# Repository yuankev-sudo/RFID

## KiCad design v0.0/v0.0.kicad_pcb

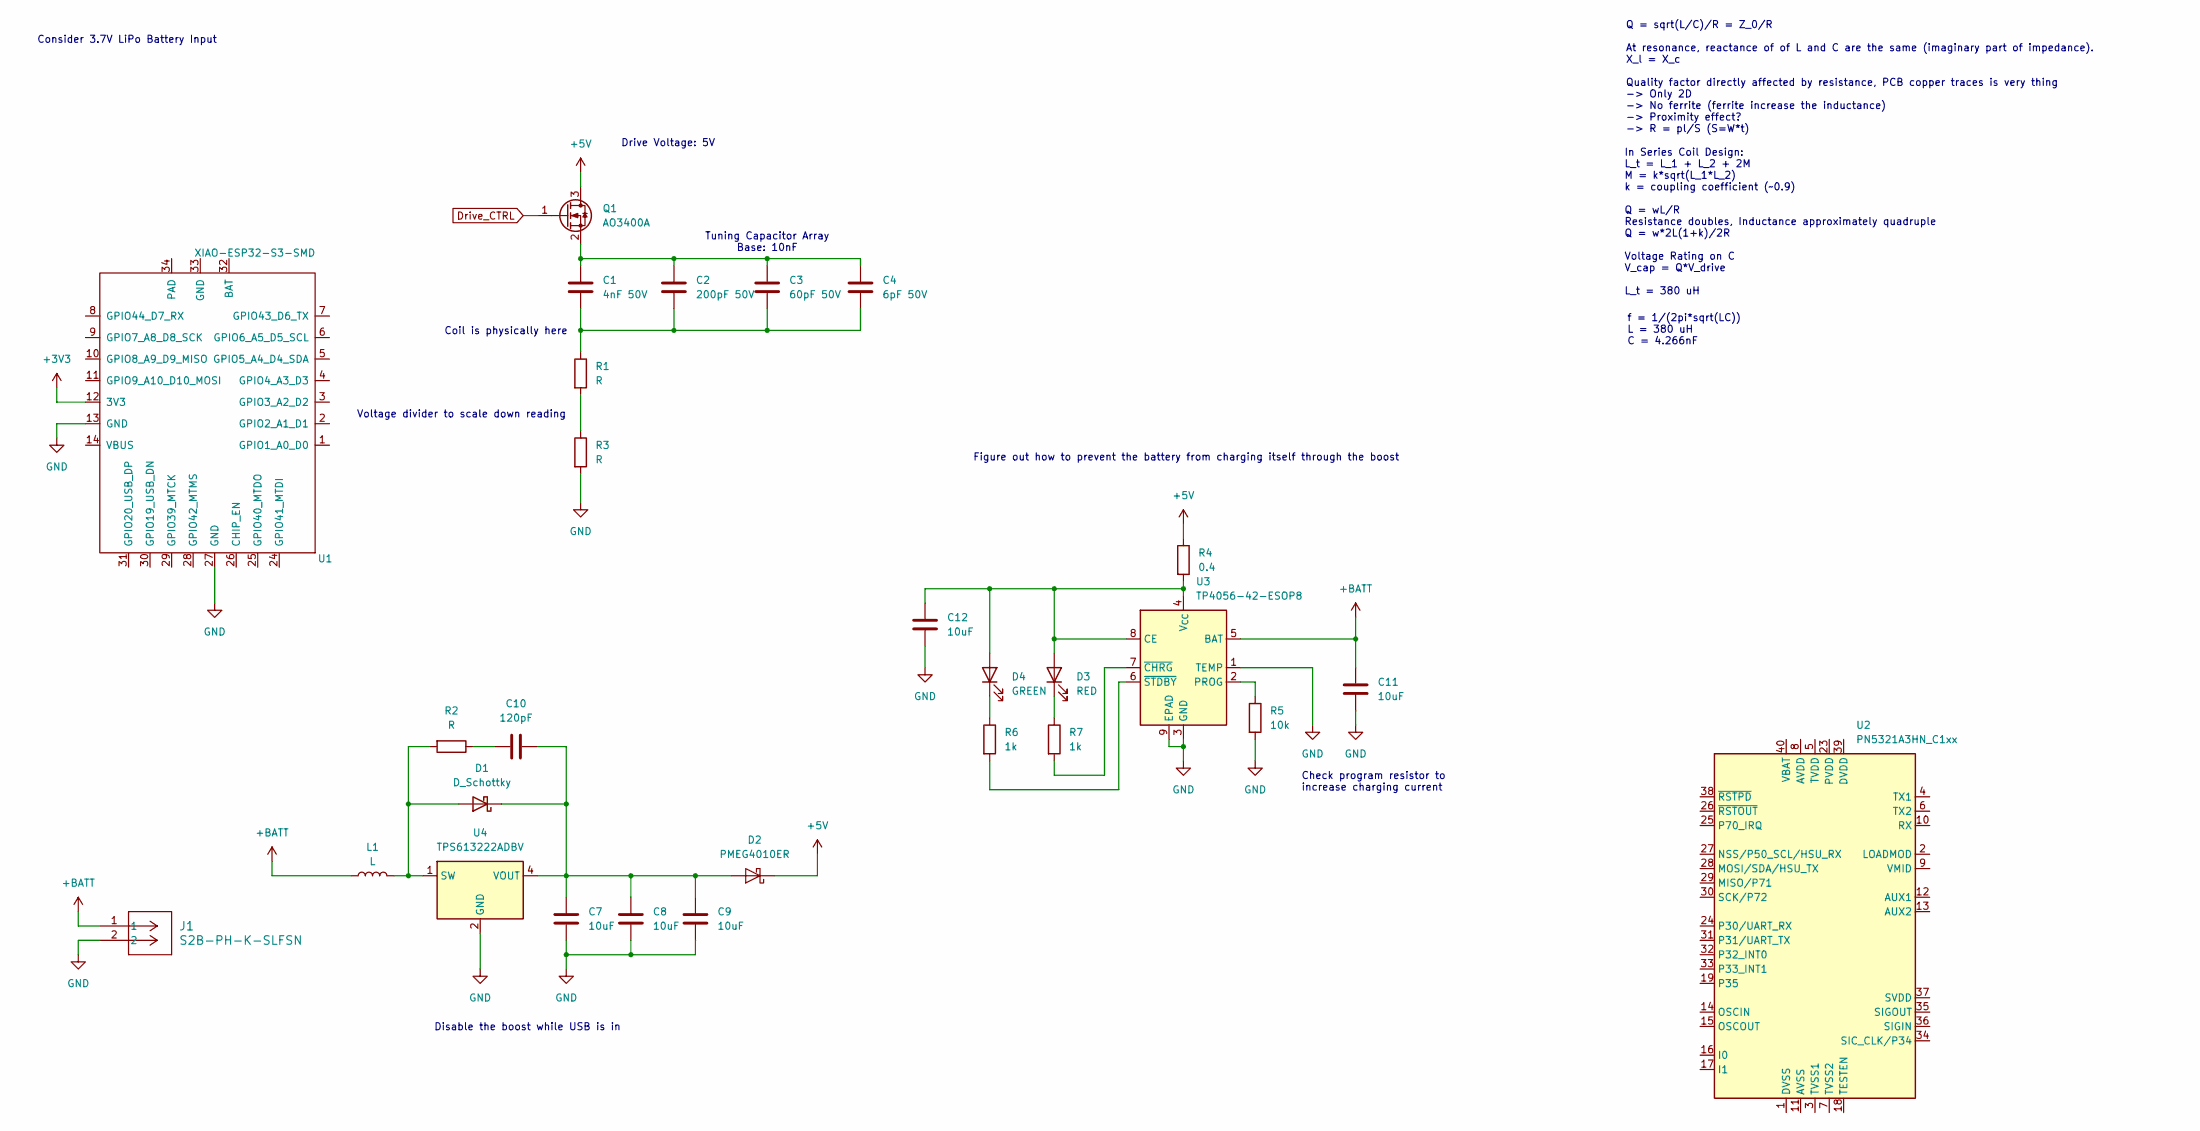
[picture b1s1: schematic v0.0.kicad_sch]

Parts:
C1: 4nF 50V; C_0805_2012Metric_Pad1.18x1.45mm_HandSolder
C2: 200pF 50V; C_0805_2012Metric_Pad1.18x1.45mm_HandSolder
C3: 60pF 50V; C_0805_2012Metric_Pad1.18x1.45mm_HandSolder
C4: 6pF 50V; C_0805_2012Metric_Pad1.18x1.45mm_HandSolder
C7, C8, C9, C11, C12: 10uF; C_0603_1608Metric
C10: 120pF; C_0603_1608Metric
D1: D_Schottky; DIODE_SOD323_1P8X1P35_ONS
D2: PMEG4010ER; Nexperia_CFP3_SOD-123W
D3: RED; LED_0603_1608Metric
D4: GREEN; LED_0603_1608Metric
J1: S2B-PH-K-SLFSN; CONN_S2B-PH-K-S_JST
L1: L; IND_DFE252012_MUR
Q1: AO3400A; SOT-23
R1, R2, R3: R; R_0603_1608Metric
R4: 0.4; R_0603_1608Metric
R5: 10k; R_0603_1608Metric
R6, R7: 1k; R_0603_1608Metric
U1: XIAO-ESP32-S3-SMD
U2: PN5321A3HN_C1xx; HVQFN-40-1EP_6x6mm_P0.5mm_EP4.1x4.1mm
U3: TP4056-42-ESOP8; SOIC-8-1EP_3.9x4.9mm_P1.27mm_EP2.41x3.3mm_ThermalVias
U4: TPS613222ADBV; SOT-23-5

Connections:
+3V3: U1.12 (3V3)
+5V: D2.1 (K), Q1.3 (D), R4.1
+BATT: C11.1, J1.1, L1.1, U3.5 (BAT)
Drive_CTRL: Q1.1 (G)
GND: C7.2, C8.2, C9.2, C11.2, C12.2, J1.2, R3.2, R5.2, U1.13 (GND), U1.27 (GND), U3.1 (TEMP), U3.3 (GND), U3.9 (EPAD), U4.2 (GND)
unnamed: C1.2, C2.2, C3.2, C4.2, R1.1
unnamed: C10.1, R2.1
unnamed: D1.2 (A), L1.2, R2.2, U4.1 (SW)
unnamed: C7.1, C8.1, C9.1, C10.2, D1.1 (K), D2.2 (A), U4.4 (VOUT)
unnamed: C12.1, D3.2 (A), D4.2 (A), R4.2, U3.4 (V_{CC}), U3.8 (CE)
unnamed: D3.1 (K), R7.1
unnamed: D4.1 (K), R6.1
unnamed: C1.1, C2.1, C3.1, C4.1, Q1.2 (S)
unnamed: R1.2, R3.1
unnamed: U2.11 (AVSS), U2.41 (AVSS)
unnamed: R5.1, U3.2 (PROG)
unnamed: R7.2, U3.7 (~CHRG)
unnamed: R6.2, U3.6 (~STDBY)

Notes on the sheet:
Q = sqrt(L/C)/R = Z_0/R At resonance, reactance of of L and C are the same (imaginary part of impedance). X_l = X_c Quality factor directly affected by resistance, PCB copper traces is very thing -> Only 2D -> No ferrite (ferrite increase the inductance) -> Proximity effect? -> R = pl/S (S=W*t)
Disable the boost while USB is in
Drive Voltage: 5V
Voltage divider to scale down reading
Figure out how to prevent the battery from charging itself through the boost
Tuning Capacitor Array Base: 10nF
f = 1/(2pi*sqrt(LC)) L = 380 uH C = 4.266nF
Check program resistor to increase charging current
Consider 3.7V LiPo Battery Input
Coil is physically here
In Series Coil Design: L_t = L_1 + L_2 + 2M M = k*sqrt(L_1*L_2) k = coupling coefficient (~0.9) Q = wL/R Resistance doubles, Inductance approximately quadruple Q = w*2L(1+k)/2R Voltage Rating on C V_cap = Q*V_drive L_t = 380 uH

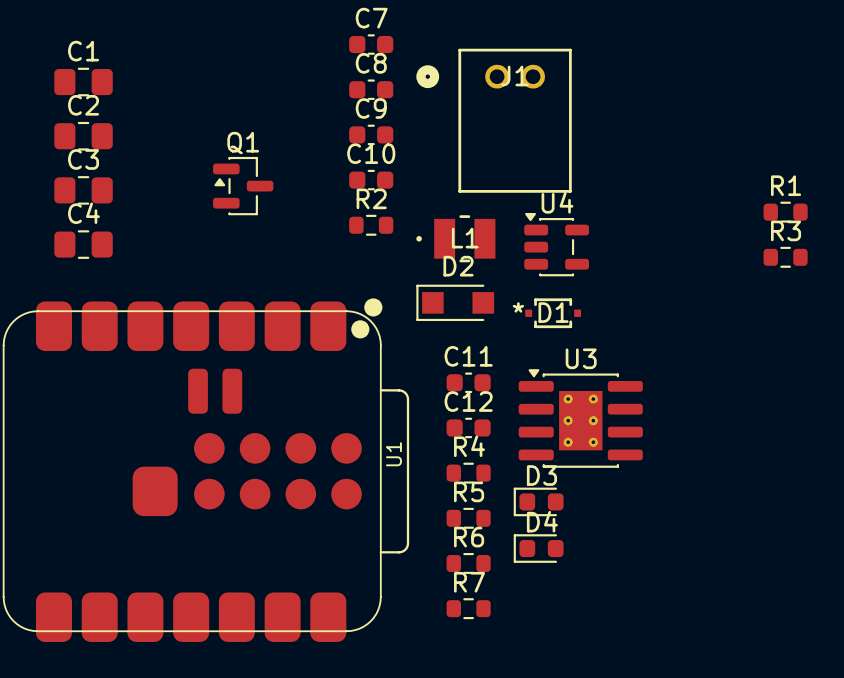
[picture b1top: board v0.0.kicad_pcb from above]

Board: 2 copper layers, 27 parts (0 on the bottom side), 15 nets.

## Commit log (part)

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2026-03-29 Add .DS_Store
2026-03-29 set up render files
